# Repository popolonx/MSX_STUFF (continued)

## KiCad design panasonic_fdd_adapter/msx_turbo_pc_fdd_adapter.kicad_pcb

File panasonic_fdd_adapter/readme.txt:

Panasonic WX/WSX/Turbo fdd adapter board.
NOTE! import footprint libraries from footprint directory.

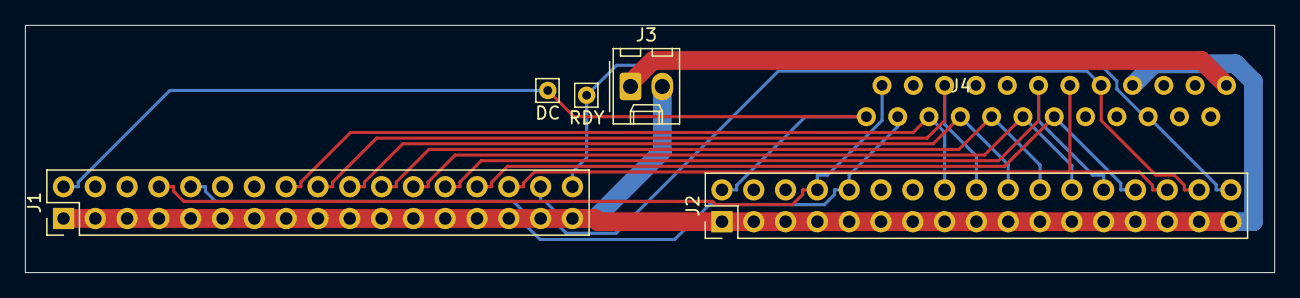
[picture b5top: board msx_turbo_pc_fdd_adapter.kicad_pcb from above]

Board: 2 copper layers, 99.8 x 19.7 mm, 6 parts (0 on the bottom side), 15 nets.

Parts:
DC: DC; Pin_D0.7mm_L6.5mm_W1.8mm_FlatFork
J1, J2: Conn_02x17_Odd_Even; PinHeader_2x17_P2.54mm_Vertical
J3: Jack-DC; Molex_KK-254_AE-6410-02A_1x02_P2.54mm_Vertical
J4: Conn_01x24_Female_fcc; 24pin_ffc_1
RDY: RDY; Pin_D0.7mm_L6.5mm_W1.8mm_FlatFork

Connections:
5V: J3.1, J4.1
24_PIN6: J1.34, J2.34, J4.6, RDY.1
24_PIN9: J1.32, J2.32, J4.9
24_PIN11: J1.30, J2.30, J4.11
24_PIN12: J1.28, J2.28, J4.12
24_PIN13: J1.26, J2.26, J4.13
24_PIN14: J1.24, J2.24, J4.14
24_PIN16: J1.22, J2.22, J4.16
24_PIN18: J1.20, J2.20, J4.18
24_PIN19: J1.18, J2.18, J4.19
24_PIN20: J1.16, J2.16, J4.20
24_PIN22: J1.10, J2.10, J4.22
24_PIN23: J1.8, J2.8, J4.23
24_PIN24: DC.1, J1.2, J2.2, J4.24
GND: J1.1, J1.3, J1.5, J1.7, J1.9, J1.11, J1.13, J1.15, J1.17, J1.19, J1.21, J1.23, J1.25, J1.27, J1.29, J1.31, J1.33, J2.1, J2.3, J2.5, J2.7, J2.9, J2.11, J2.13, J2.15, J2.17, J2.19, J2.21, J2.23, J2.25, J2.27, J2.29, J2.31, J2.33, J3.2, J4.7
